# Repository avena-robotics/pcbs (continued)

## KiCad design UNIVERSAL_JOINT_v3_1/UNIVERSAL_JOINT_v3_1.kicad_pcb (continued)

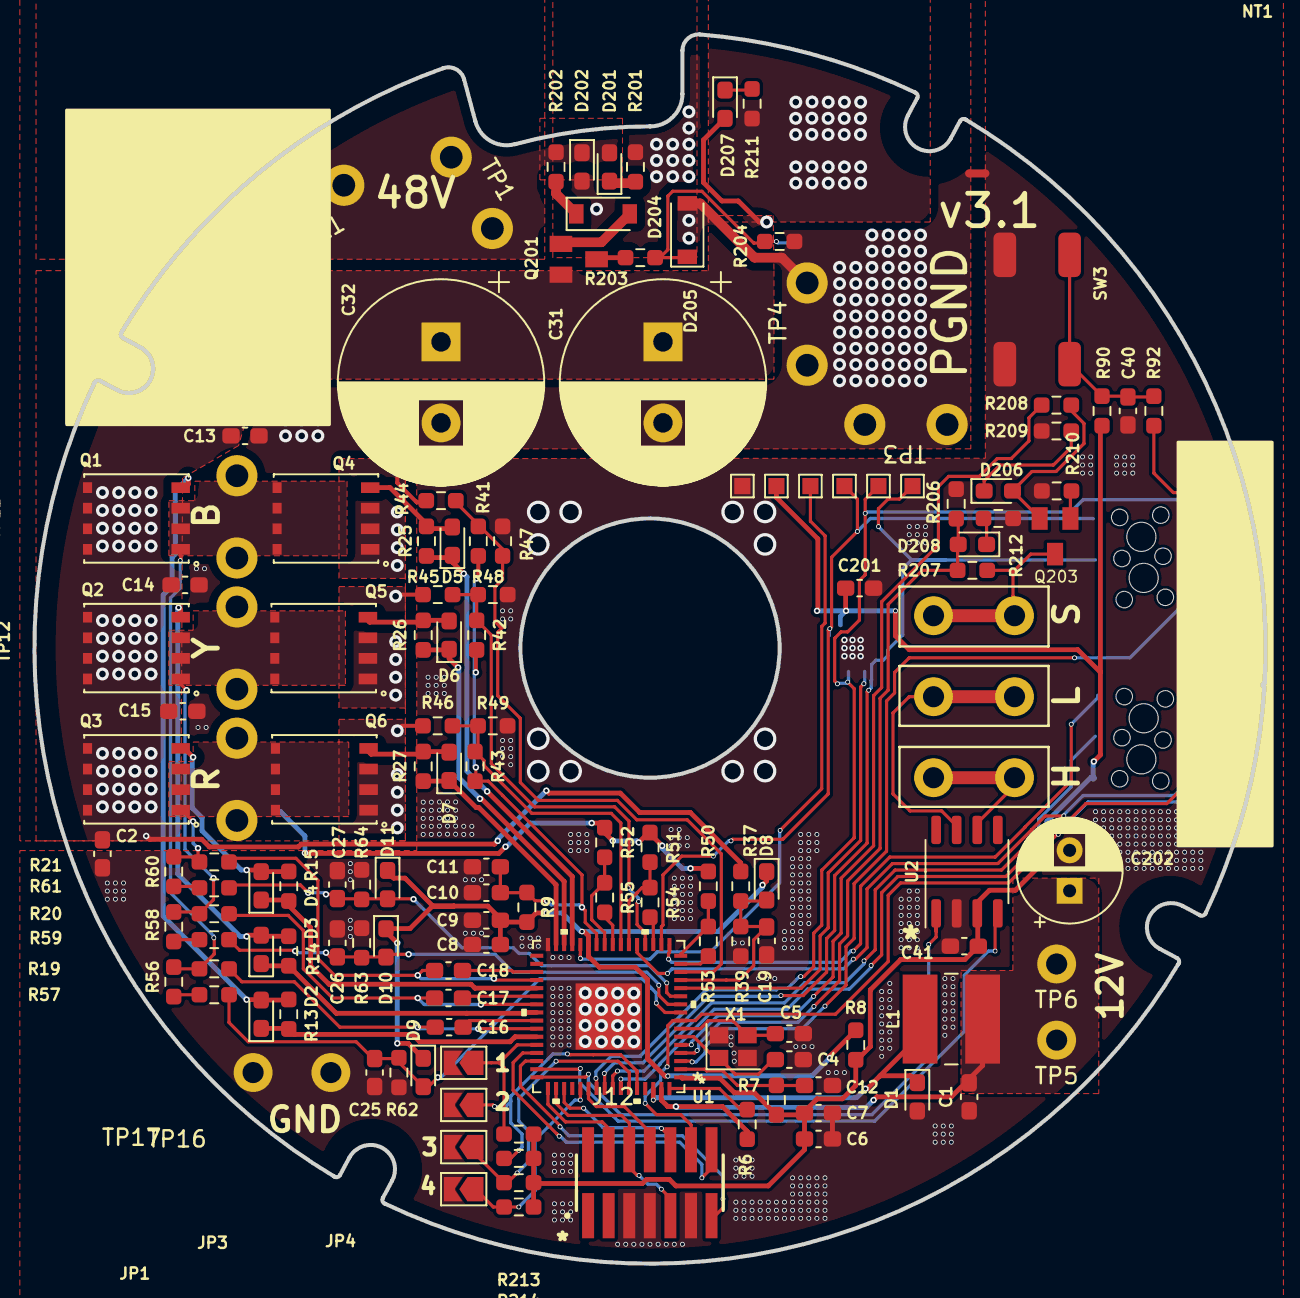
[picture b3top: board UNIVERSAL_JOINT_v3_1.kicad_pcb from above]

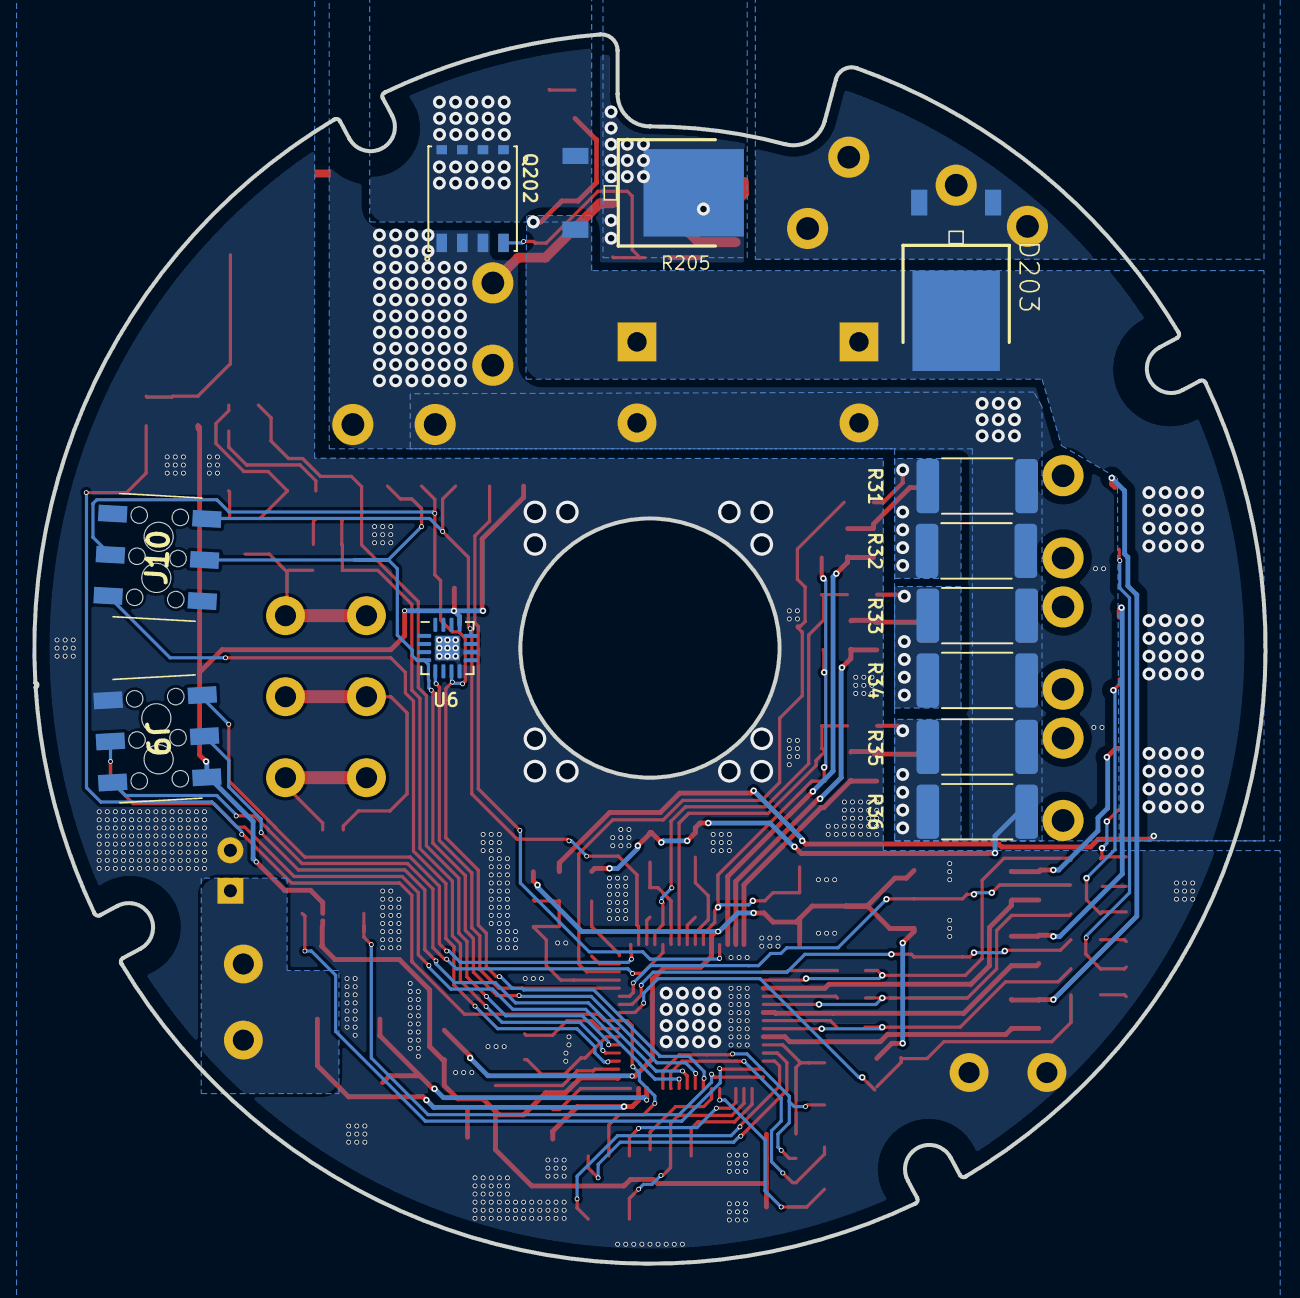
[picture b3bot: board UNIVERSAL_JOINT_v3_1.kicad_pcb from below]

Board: 2 copper layers, 76.0 x 75.9 mm, 155 parts (12 on the bottom side), 93 nets.
